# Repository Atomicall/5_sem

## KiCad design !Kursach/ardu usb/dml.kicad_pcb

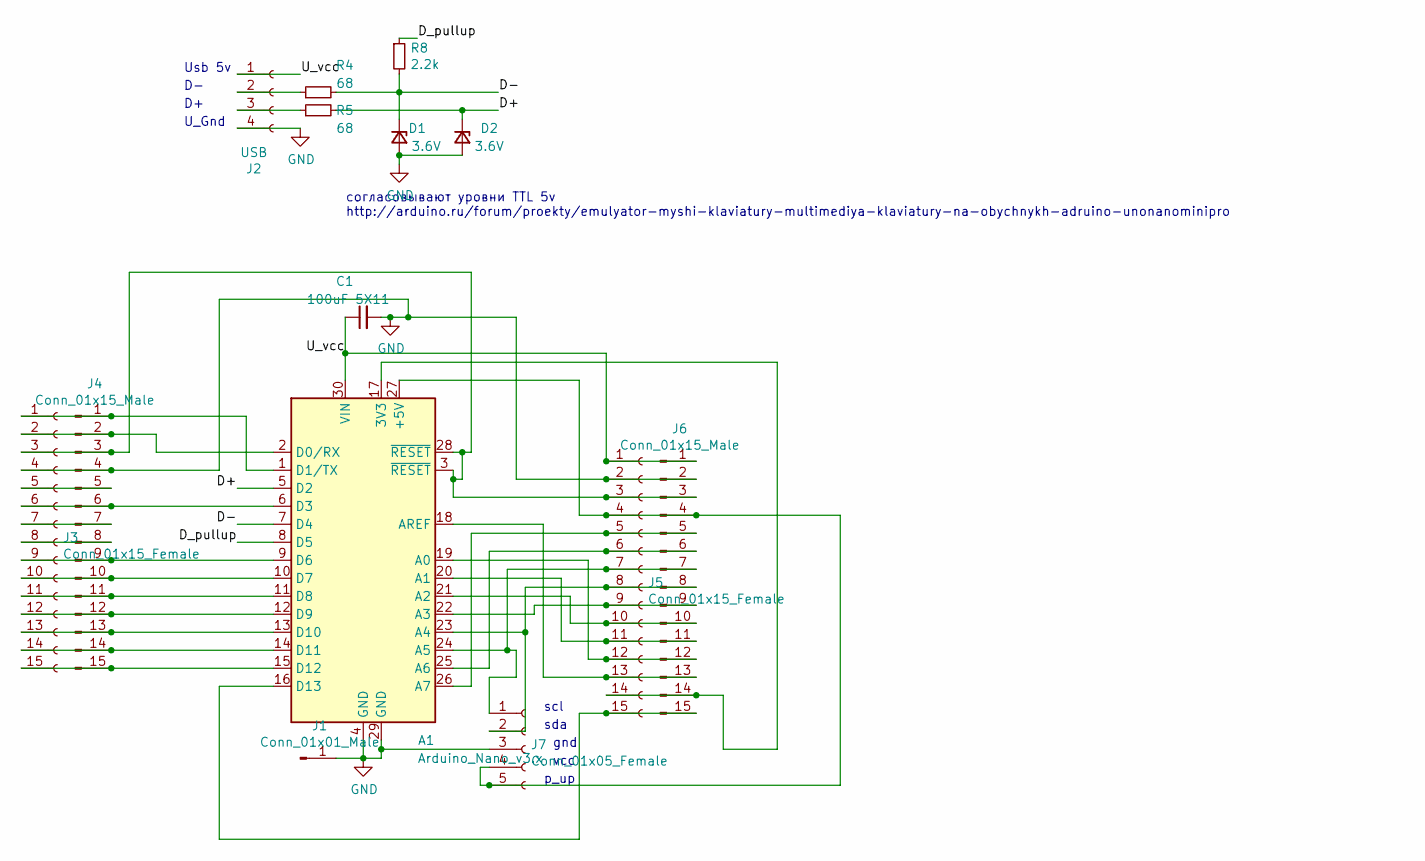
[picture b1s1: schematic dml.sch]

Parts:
A1: Arduino_Nano_v3.x; Arduino_Nano
C1: 100uF 5X11; C_Radial_D5.0mm_H11.0mm_P2.00mm
D1, D2: 3.6V; D_DO-35_SOD27_P7.62mm_Horizontal
J1: Conn_01x01_Male; PinSocket_1x01_P2.54mm_Vertical
J2: USB; usb_type_c_female_board_Aliexpress
J3, J5: Conn_01x15_Female; PinSocket_1x15_P2.54mm_Vertical
J4, J6: Conn_01x15_Male; PinSocket_1x15_P2.54mm_Vertical
J7: Conn_01x05_Female; PinSocket_1x05_P2.54mm_Vertical
R4, R5: 68; R_Axial_DIN0204_L3.6mm_D1.6mm_P2.54mm_Vertical
R8: 2.2k; R_Axial_DIN0204_L3.6mm_D1.6mm_P2.54mm_Vertical

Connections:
/D+: A1.5 (D2), D2.1 (K), R5.2
/D-: A1.7 (D4), D1.1 (K), R4.2, R8.2
/D_pullup: A1.8 (D5), R8.1
/U_vcc: A1.30 (VIN), C1.1, J2.1, J5.1, J6.1
GND: A1.4 (GND), A1.29 (GND), C1.2, D1.2 (A), D2.2 (A), J1.1, J2.4, J3.4, J4.4, J5.2, J6.2, J7.3
unnamed: A1.1 (D1/TX), J3.1, J4.1
unnamed: A1.2 (D0/RX), J3.2, J4.2
unnamed: A1.6 (D3), J3.6, J4.6
unnamed: A1.9 (D6), J3.9, J4.9
unnamed: A1.10 (D7), J3.10, J4.10
unnamed: A1.11 (D8), J3.11, J4.11
unnamed: A1.12 (D9), J3.12, J4.12
unnamed: A1.13 (D10), J3.13, J4.13
unnamed: A1.14 (D11), J3.14, J4.14
unnamed: A1.15 (D12), J3.15, J4.15
unnamed: A1.16 (D13), J5.15, J6.15
unnamed: A1.17 (3V3), J5.14, J6.14
unnamed: A1.18 (AREF), J5.13, J6.13
unnamed: A1.19 (A0), J5.12, J6.12
unnamed: A1.20 (A1), J5.11, J6.11
unnamed: A1.21 (A2), J5.10, J6.10
unnamed: A1.22 (A3), J5.9, J6.9
unnamed: A1.23 (A4), J5.8, J6.8, J7.2
unnamed: A1.24 (A5), J5.7, J6.7, J7.1
unnamed: A1.25 (A6), J5.6, J6.6
unnamed: A1.26 (A7), J5.5, J6.5
unnamed: A1.27 (+5V), J5.4, J6.4, J7.4, J7.5
unnamed: A1.3 (~RESET), A1.28 (~RESET), J3.3, J4.3, J5.3, J6.3
unnamed: J2.2, R4.1
unnamed: J2.3, R5.1
unnamed: J3.5, J4.5
unnamed: J3.7, J4.7
unnamed: J3.8, J4.8

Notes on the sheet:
Usb 5v
U_Gnd
согласовывают уровни TTL 5v http://arduino.ru/forum/proekty/emulyator-myshi-klaviatury-multimediya-klaviatury-na-obychnykh-adruino-unonanominipro
scl
sda
gnd
vcc
p_up

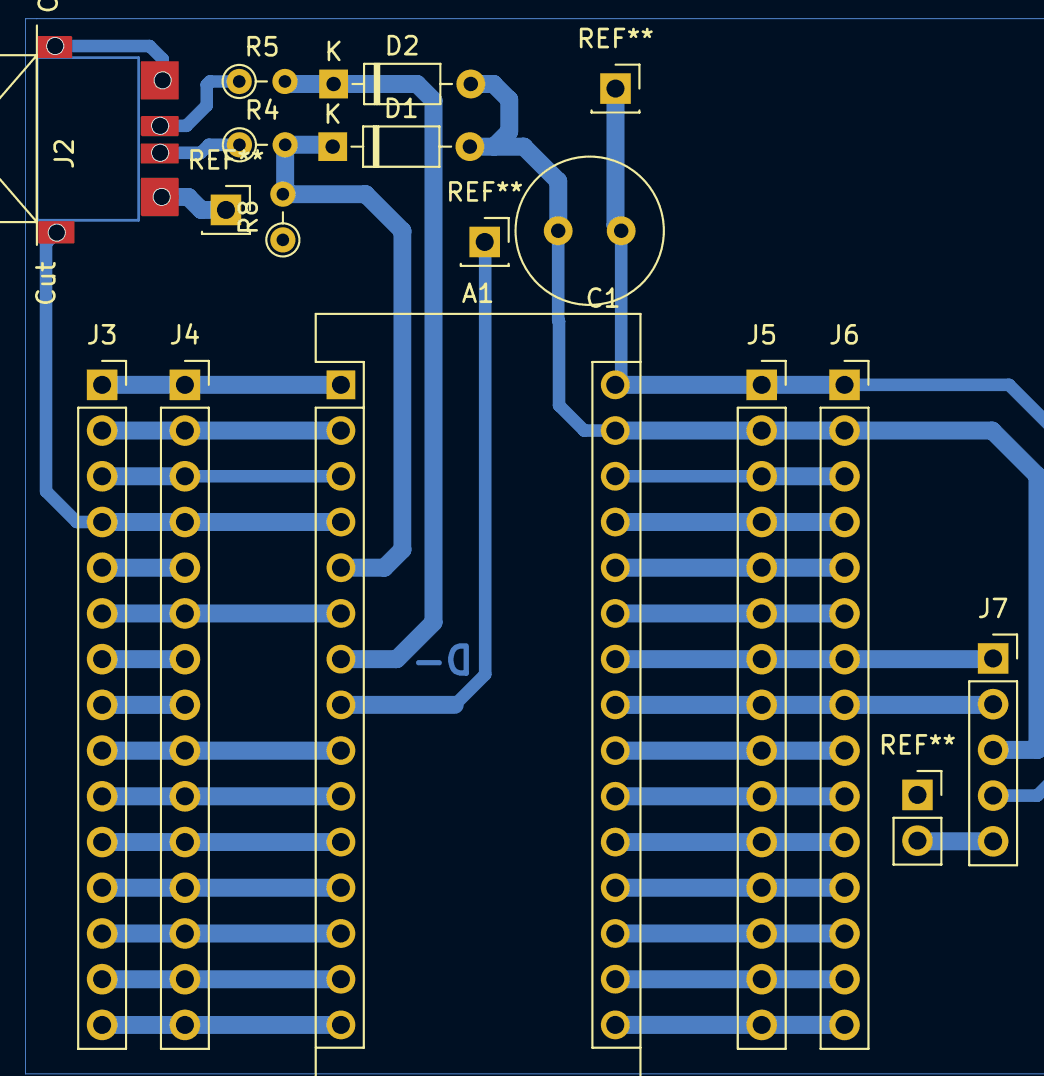
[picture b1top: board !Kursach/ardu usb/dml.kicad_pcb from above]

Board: 2 copper layers, 13 parts (0 on the bottom side), 33 nets.

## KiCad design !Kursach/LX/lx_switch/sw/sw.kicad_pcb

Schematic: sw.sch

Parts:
D1: ss14; D_SMB_Handsoldering
J1: bat; PinSocket_1x02_P2.54mm_Horizontal
J2: usb; PinSocket_1x02_P2.54mm_Horizontal
J3: out; PinSocket_1x02_P2.54mm_Horizontal
Q1: AO3401A; SOT-23
R1: 2.2k; R_1206_3216Metric_Pad1.30x1.75mm_HandSolder

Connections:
GND: J1.2, J2.2, J3.1, R1.2
unnamed: D1.1 (K), J3.2, Q1.2 (S)
unnamed: D1.2 (A), J2.1, Q1.1 (G), R1.1
unnamed: J1.1, Q1.3 (D)

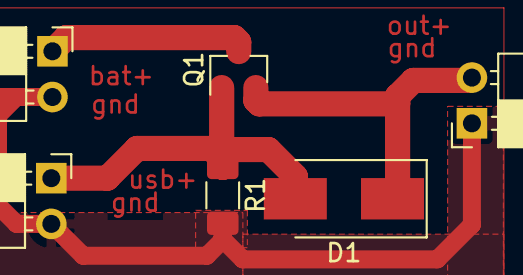
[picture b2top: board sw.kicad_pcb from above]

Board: 2 copper layers, 6 parts (0 on the bottom side), 4 nets.

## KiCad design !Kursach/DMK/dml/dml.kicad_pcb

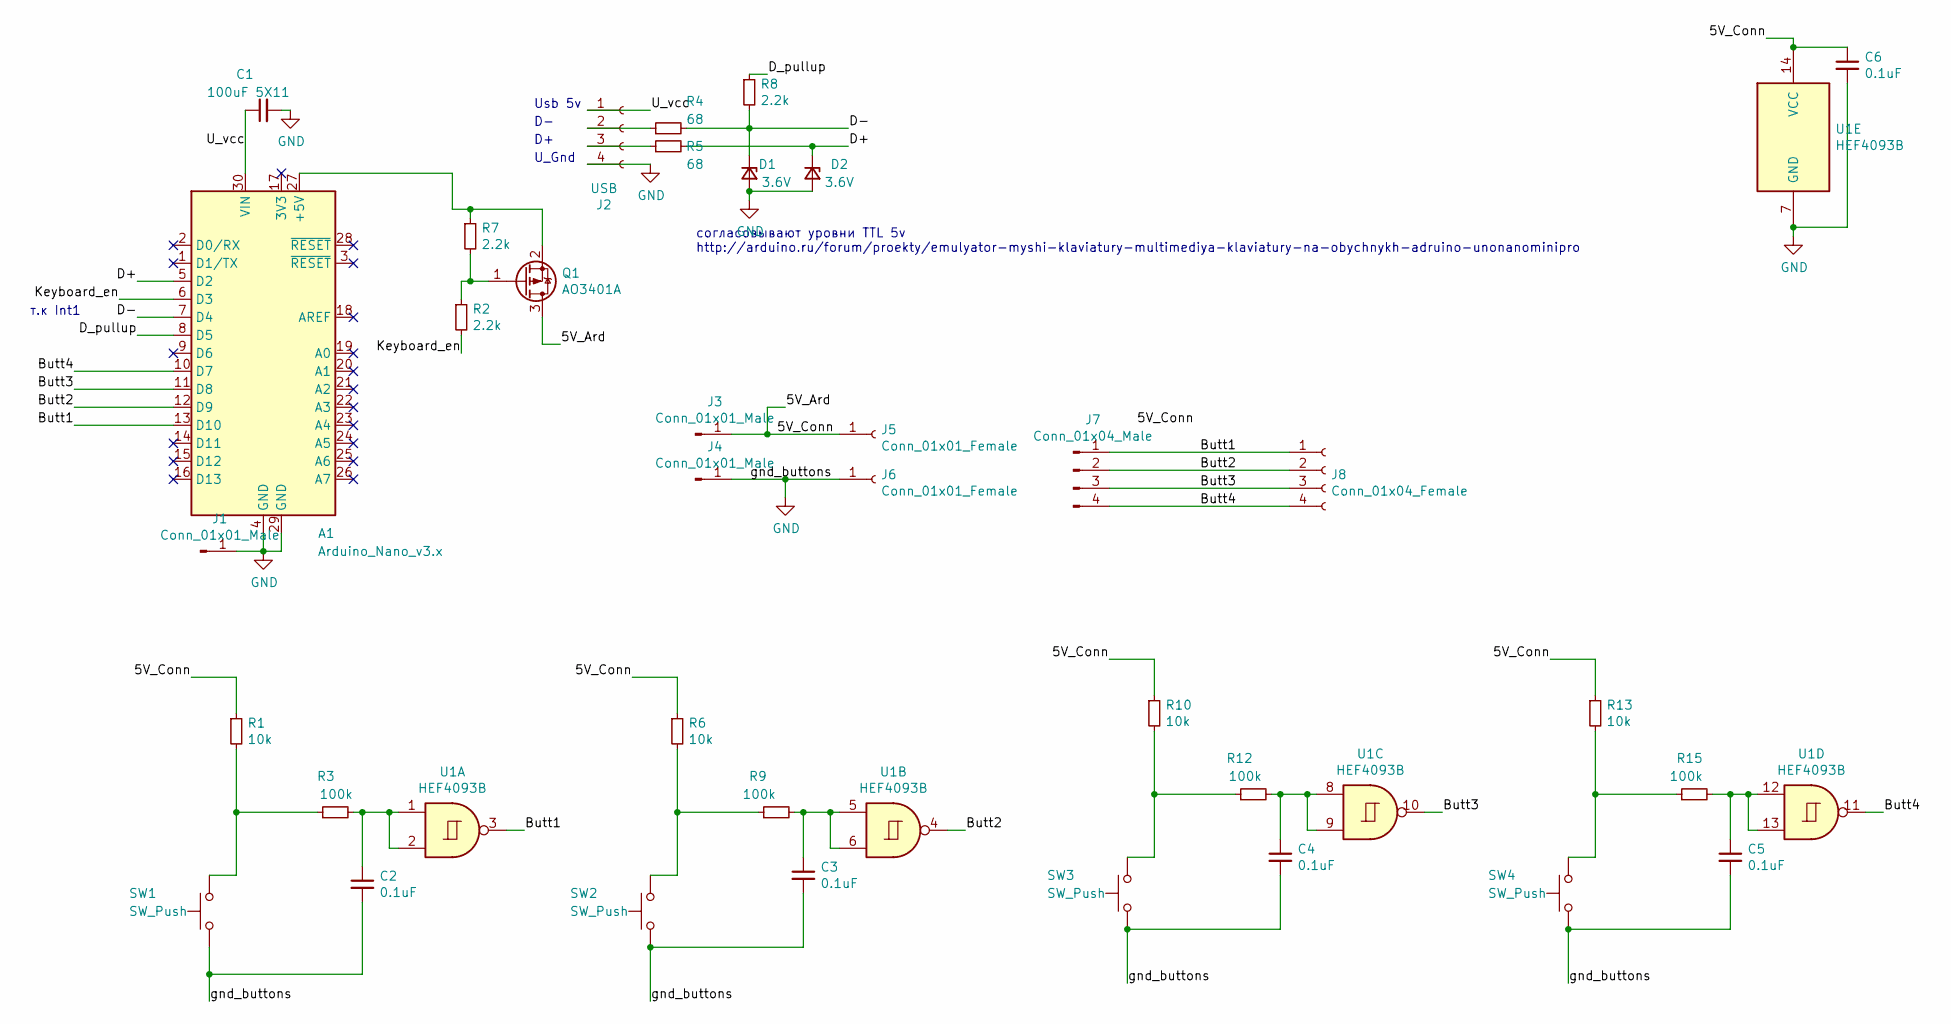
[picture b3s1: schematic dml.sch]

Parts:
A1: Arduino_Nano_v3.x; Arduino_Nano
C1: 100uF 5X11; C_Radial_D5.0mm_H11.0mm_P2.00mm
C2, C3, C4, C5, C6: 0.1uF; C_0805_2012Metric_Pad1.18x1.45mm_HandSolder
D1, D2: 3.6V; D_DO-35_SOD27_P7.62mm_Horizontal
J1: Conn_01x01_Male; PinSocket_1x01_P2.54mm_Vertical
J2: USB; usb_type_c_female_board_Aliexpress
J3, J4: Conn_01x01_Male; PinHeader_1x01_P2.54mm_Vertical
J5, J6: Conn_01x01_Female; PinHeader_1x01_P2.54mm_Vertical
J7: Conn_01x04_Male; PinHeader_1x04_P2.54mm_Vertical
J8: Conn_01x04_Female; PinHeader_1x04_P2.54mm_Vertical
Q1: AO3401A; SOT-23
R1, R6, R10, R13: 10k; R_0805_2012Metric_Pad1.20x1.40mm_HandSolder
R2, R7: 2.2k; R_0805_2012Metric_Pad1.20x1.40mm_HandSolder
R3, R9, R12, R15: 100k; R_0805_2012Metric_Pad1.20x1.40mm_HandSolder
R4, R5: 68; R_Axial_DIN0204_L3.6mm_D1.6mm_P2.54mm_Vertical
R8: 2.2k; R_Axial_DIN0204_L3.6mm_D1.6mm_P2.54mm_Vertical
SW1, SW2, SW3, SW4: SW_Push; SW_Cherry_MX_1.00u_Plate
U1: HEF4093B; SO-14_3.9x8.65mm_P1.27mm

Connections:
/5V_Ard: C6.1, J3.1, J5.1, Q1.3 (D), R1.1, R6.1, R10.1, R13.1, U1.14 (VCC)
/Butt1: A1.13 (D10), J7.1, J8.1, U1.3
/Butt2: A1.12 (D9), J7.2, J8.2, U1.4
/Butt3: A1.11 (D8), J7.3, J8.3, U1.10
/Butt4: A1.10 (D7), J7.4, J8.4, U1.11
/D+: A1.5 (D2), D2.1 (K), R5.2
/D-: A1.7 (D4), D1.1 (K), R4.2, R8.2
/D_pullup: A1.8 (D5), R8.1
/Keyboard_en: A1.6 (D3), R2.2
/U_vcc: A1.30 (VIN), C1.1, J2.1
GND: A1.4 (GND), A1.29 (GND), C1.2, C2.2, C3.2, C4.2, C5.2, C6.2, D1.2 (A), D2.2 (A), J1.1, J2.4, J4.1, J6.1, SW1.1, SW2.1, SW3.1, SW4.1, U1.7 (GND)
unnamed: A1.27 (+5V), Q1.2 (S), R7.1
unnamed: C2.1, R3.2, U1.1, U1.2
unnamed: C3.1, R9.2, U1.5, U1.6
unnamed: C4.1, R12.2, U1.8, U1.9
unnamed: C5.1, R15.2, U1.12, U1.13
unnamed: J2.2, R4.1
unnamed: J2.3, R5.1
unnamed: Q1.1 (G), R2.1, R7.2
unnamed: R1.2, R3.1, SW1.2
unnamed: R6.2, R9.1, SW2.2
unnamed: R10.2, R12.1, SW3.2
unnamed: R13.2, R15.1, SW4.2

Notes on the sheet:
Usb 5v
U_Gnd
согласовывают уровни TTL 5v http://arduino.ru/forum/proekty/emulyator-myshi-klaviatury-multimediya-klaviatury-na-obychnykh-adruino-unonanominipro
т.к Int1

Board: 2 copper layers, 35 parts (0 on the bottom side), 23 nets, no tracks yet.

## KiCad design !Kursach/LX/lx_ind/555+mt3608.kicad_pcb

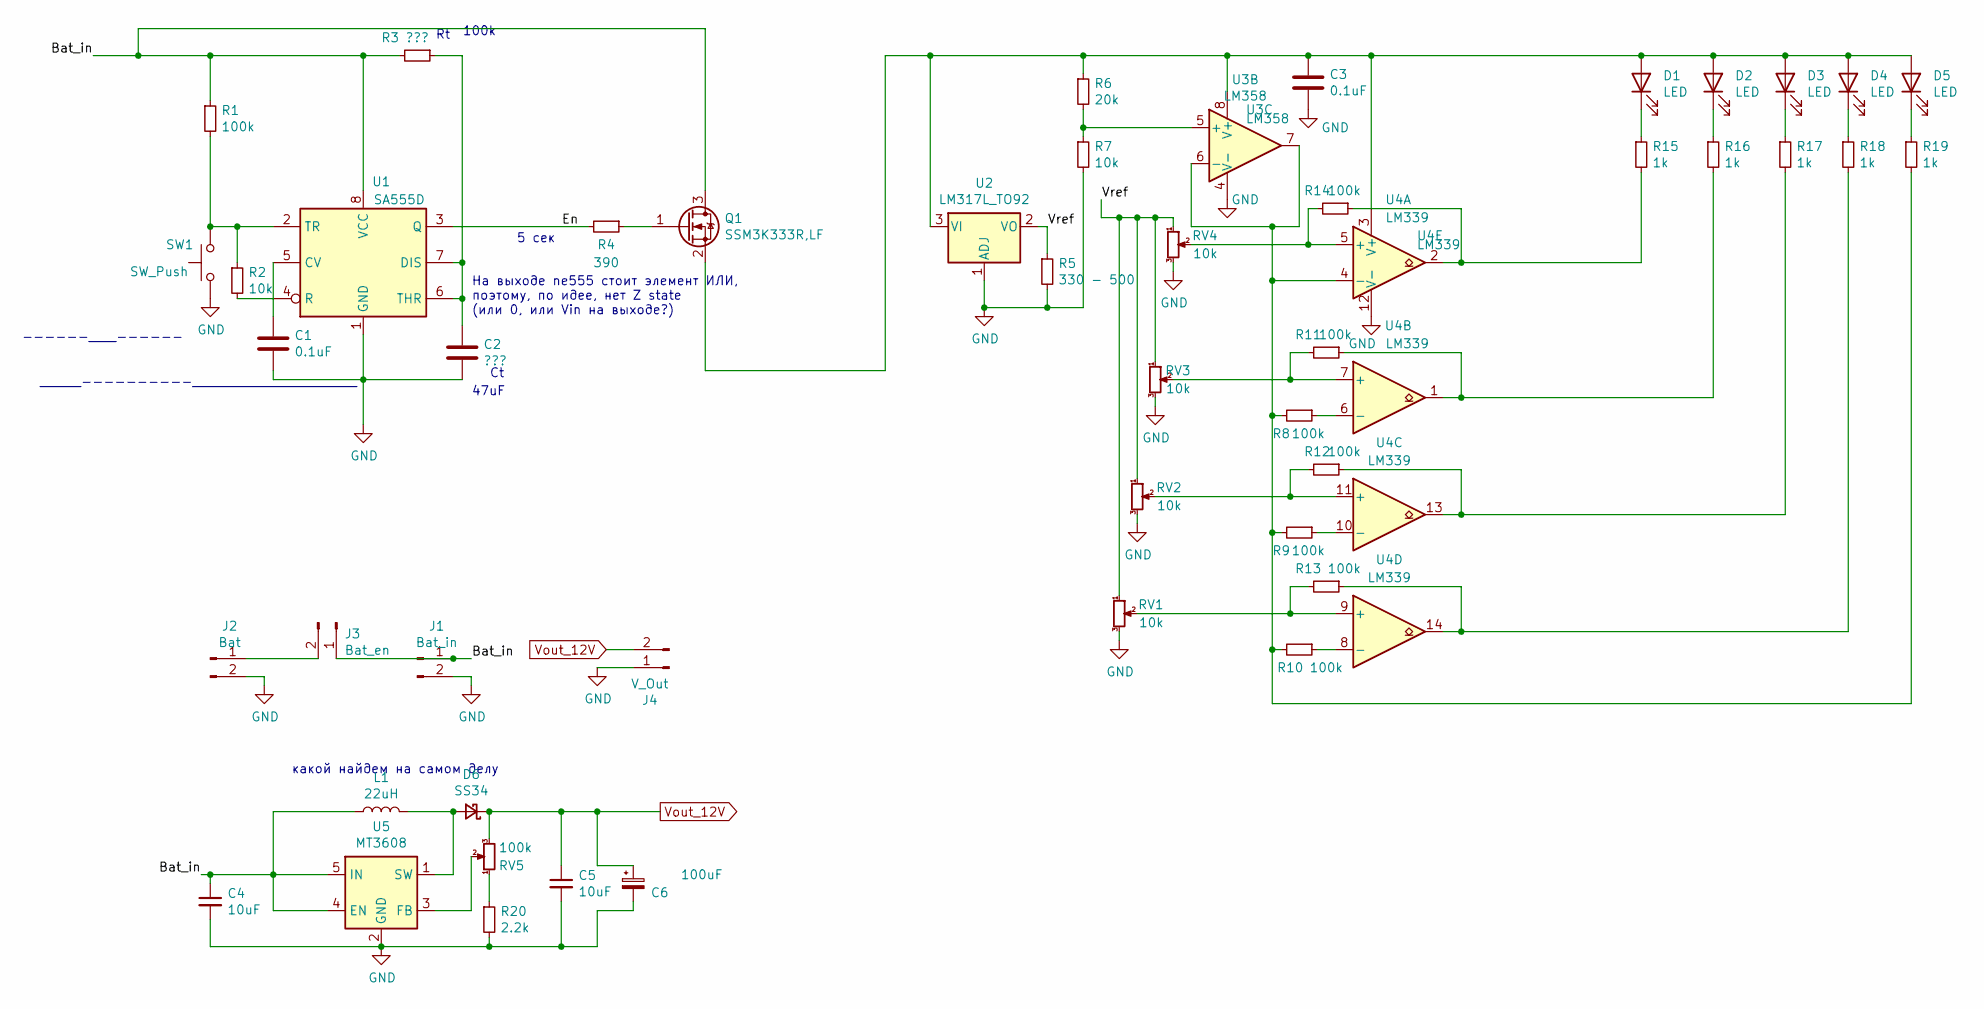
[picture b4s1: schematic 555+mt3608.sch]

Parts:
C1, C3: 0.1uF; C_1206_3216Metric_Pad1.33x1.80mm_HandSolder
C2: ???; CP_EIA-3216-10_Kemet-I_Pad1.58x1.35mm_HandSolder
C4, C5: 10uF; C_1206_3216Metric_Pad1.33x1.80mm_HandSolder
C6: 100uF; CP_Radial_D10.0mm_P5.00mm
D1, D2, D3, D4, D5: LED; LED_1206_3216Metric_Pad1.42x1.75mm_HandSolder
D6: SS34; D_SMC
J1: Bat_in; PinSocket_1x02_P2.54mm_Horizontal
J2: Bat; PinSocket_1x02_P2.54mm_Horizontal
J3: Bat_en; PinSocket_1x02_P2.54mm_Horizontal
J4: V_Out; PinSocket_1x02_P2.54mm_Horizontal
L1: 22uH; L_Bourns_SRR1210A
Q1: SSM3K333R,LF; SOT-23
R1, R8, R9, R10, R11, R12, R13, R14: 100k; R_1206_3216Metric_Pad1.30x1.75mm_HandSolder
R2, R7: 10k; R_1206_3216Metric_Pad1.30x1.75mm_HandSolder
R3: ???; R_1206_3216Metric_Pad1.30x1.75mm_HandSolder
R4: 390; R_1206_3216Metric_Pad1.30x1.75mm_HandSolder
R5: 330 - 500; R_1206_3216Metric_Pad1.30x1.75mm_HandSolder
R6: 20k; R_1206_3216Metric_Pad1.30x1.75mm_HandSolder
R15, R16, R17, R18, R19: 1k; R_1206_3216Metric_Pad1.30x1.75mm_HandSolder
R20: 2.2k; R_1206_3216Metric_Pad1.30x1.75mm_HandSolder
RV1, RV2, RV3, RV4: 10k; Potentiometer_Bourns_TC33X_Vertical
RV5: 100k; Potentiometer_Bourns_TC33X_Vertical
SW1: SW_Push; SW_SPST_EVPBF
U1: SA555D; SOIC-8_3.9x4.9mm_P1.27mm
U2: LM317L_TO92; TO-92_Inline
U3: LM358; SO-8_3.9x4.9mm_P1.27mm
U4: LM339; SO-14_3.9x8.65mm_P1.27mm
U5: MT3608; SOT-23-6_Handsoldering

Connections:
/Bat_in: C4.1, J1.1, J3.1, L1.1, Q1.3 (D), R1.1, R3.2, U1.8 (VCC), U5.4 (EN), U5.5 (IN)
/En: R4.2, U1.3 (Q)
/Vref: R5.1, RV1.1, RV2.1, RV3.1, RV4.1, U2.2 (VO)
GND: C1.2, C2.2, C3.2, C4.2, C5.2, C6.2, J1.2, J2.2, J4.1, R5.2, R7.2, R20.2, RV1.3, RV2.3, RV3.3, RV4.3, SW1.1, U1.1 (GND), U2.1 (ADJ), U3.4 (V-), U4.12 (V-), U5.2 (GND)
unnamed: C1.1, U1.5 (CV)
unnamed: C2.1, R3.1, U1.6 (THR), U1.7 (DIS)
unnamed: C3.1, D1.2 (A), D2.2 (A), D3.2 (A), D4.2 (A), D5.2 (A), Q1.2 (S), R6.1, U2.3 (VI), U3.8 (V+), U4.3 (V+)
unnamed: D1.1 (K), R15.1
unnamed: D2.1 (K), R16.1
unnamed: D3.1 (K), R17.1
unnamed: D4.1 (K), R18.1
unnamed: D5.1 (K), R19.1
unnamed: D6.2 (A), L1.2, U5.1 (SW)
unnamed: J2.1, J3.2
unnamed: Q1.1 (G), R4.1
unnamed: R1.2, R2.1, SW1.2, U1.2 (TR)
unnamed: R2.2, U1.4 (R)
unnamed: R6.2, R7.1, U3.5 (+)
unnamed: R8.1, U4.6 (-)
unnamed: R9.1, U4.10 (-)
unnamed: R10.1, U4.8 (-)
unnamed: R8.2, R9.2, R10.2, R19.2, U3.6 (-), U3.7, U4.4 (-)
unnamed: R11.1, R16.2, U4.1
unnamed: R11.2, RV3.2, U4.7 (+)
unnamed: R12.1, R17.2, U4.13
unnamed: R12.2, RV2.2, U4.11 (+)
unnamed: R13.1, R18.2, U4.14
unnamed: R13.2, RV1.2, U4.9 (+)
unnamed: R14.1, R15.2, U4.2
unnamed: R14.2, RV4.2, U4.5 (+)
unnamed: R20.1, RV5.1
unnamed: RV5.2, U5.3 (FB)
Vout_12V: C5.1, C6.1, D6.1 (K), J4.2, RV5.3

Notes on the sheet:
------____------
______----------________________________
100k
47uF
5 сек
На выходе ne555 стоит элемент ИЛИ, поэтому, по идее, нет Z state (или 0, или Vin на выходе?)
какой найдем на самом делу

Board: 2 copper layers, 49 parts (0 on the bottom side), 33 nets, no tracks yet.

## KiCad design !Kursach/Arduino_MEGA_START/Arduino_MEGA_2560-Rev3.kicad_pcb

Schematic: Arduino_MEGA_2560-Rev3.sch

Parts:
ADCH1: 8x1F-H8.5; SMARTPRJ_1X08
ADCL1: 8x1F-H8.5; SMARTPRJ_1X08
COMMUNICATION1: 8x1F-H8.5; SMARTPRJ_1X08
J1: RX; PinHeader_1x02_P2.54mm_Vertical
J2: TX; PinHeader_1x02_P2.54mm_Vertical
J3: Midi_UART; PinHeader_1x03_P2.54mm_Vertical
J4: USB_Uart; PinHeader_1x03_P2.54mm_Vertical
J5: Power_conn; PinHeader_1x02_P2.54mm_Vertical
POWER1: 8x1F-H8.5; SMARTPRJ_1X08
PWMH1: 8x1F-H8.5; PinHeader_1x08_P2.54mm_Vertical
PWML1: 8x1F-H8.5; SMARTPRJ_1X08
XIO1: 18x2F-H8.5; SMARTPRJ_2X18

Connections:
/+3V3: POWER1.4
/+5V: POWER1.2, POWER1.5
/ADC0: ADCL1.1
/ADC1: ADCL1.2
/ADC2: ADCL1.3
/ADC3: ADCL1.4
/ADC4: ADCL1.5
/ADC5: ADCL1.6
/ADC6: ADCL1.7
/ADC7: ADCL1.8
/ADC8: ADCH1.1
/ADC9: ADCH1.2
/ADC10: ADCH1.3
/ADC11: ADCH1.4
/ADC12: ADCH1.5
/ADC13: ADCH1.6
/ADC14: ADCH1.7
/ADC15: ADCH1.8
/Aref: PWMH1.8
/Dir1: XIO1.3; also elsewhere on the board
/Dir2: XIO1.7; also elsewhere on the board
/Dir3: XIO1.11; also elsewhere on the board
/Dir4: XIO1.15; also elsewhere on the board
/Dir5: XIO1.19; also elsewhere on the board
/Dir6: XIO1.23; also elsewhere on the board
/Dir7: XIO1.27; also elsewhere on the board
/Dir8: XIO1.31; also elsewhere on the board
/Dir9: XIO1.4; also elsewhere on the board
/Dir10: XIO1.8; also elsewhere on the board
/Dir11: XIO1.12; also elsewhere on the board
/Dir12: XIO1.16; also elsewhere on the board
/Dir13: XIO1.20; also elsewhere on the board
/Dir14: XIO1.24; also elsewhere on the board
/Dir15: XIO1.28; also elsewhere on the board
/Dir16: XIO1.32; also elsewhere on the board
/Dir17: PWML1.3; also elsewhere on the board
/Dir18: PWML1.5; also elsewhere on the board
/P24: XIO1.5; also elsewhere on the board
/P25: XIO1.6; also elsewhere on the board
/P28: XIO1.9; also elsewhere on the board
/P29: XIO1.10; also elsewhere on the board
/P32: XIO1.13; also elsewhere on the board
/P33: XIO1.14; also elsewhere on the board
/P36: XIO1.17; also elsewhere on the board
/P37: XIO1.18; also elsewhere on the board
/P40: XIO1.21; also elsewhere on the board
/P41: XIO1.22; also elsewhere on the board
/P44: XIO1.25; also elsewhere on the board
/P45: XIO1.26; also elsewhere on the board
/P48: XIO1.29; also elsewhere on the board
/P49: XIO1.30; also elsewhere on the board
/P52: XIO1.33; also elsewhere on the board
/P53: XIO1.34; also elsewhere on the board
/PB4: PWMH1.3
/PB5: PWMH1.4
/PB6: PWMH1.5
/PB7: PWMH1.6
/PE0: J1.2, PWML1.1
/PE1: J2.2, PWML1.2
/PE3: PWML1.6; also elsewhere on the board
/PE5: PWML1.4; also elsewhere on the board
/PH3: PWML1.7
/PH4: PWML1.8
/PH5: PWMH1.1
/PH6: PWMH1.2
/RESET: POWER1.3
/RXD1: COMMUNICATION1.3
/RXD2: COMMUNICATION1.5, J4.2
/RXD3: COMMUNICATION1.7, J3.2
/SCL: COMMUNICATION1.1
/SDA: COMMUNICATION1.2
/TXD1: COMMUNICATION1.4
/TXD2: COMMUNICATION1.6, J4.3
/TXD3: COMMUNICATION1.8, J3.3
/VIN: J5.2, POWER1.8
GND: J3.1, J4.1, J5.1, POWER1.6, POWER1.7, PWMH1.7, XIO1.35, XIO1.36

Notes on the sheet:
AREF

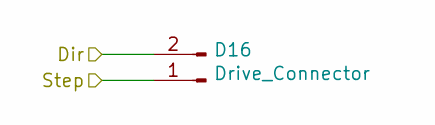
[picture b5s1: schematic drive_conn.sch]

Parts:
D1: Drive_Connector; PinHeader_1x02_P2.54mm_Vertical

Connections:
/Dir1: D1.2; also elsewhere on the board
/P24: D1.1; also elsewhere on the board

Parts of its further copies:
D2, D3, D4, D5, D6, D7, D8, D9, D10, D11, D12, D13, D14, D15, D16, D17, D18: Drive_Connector; PinHeader_1x02_P2.54mm_Vertical

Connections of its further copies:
/Dir2: D2.2; also elsewhere on the board
/Dir3: D3.2; also elsewhere on the board
/Dir4: D4.2; also elsewhere on the board
/Dir5: D5.2; also elsewhere on the board
/Dir6: D6.2; also elsewhere on the board
/Dir7: D7.2; also elsewhere on the board
/Dir8: D8.2; also elsewhere on the board
/Dir9: D9.2; also elsewhere on the board
/Dir10: D10.2; also elsewhere on the board
/Dir11: D11.2; also elsewhere on the board
/Dir12: D12.2; also elsewhere on the board
/Dir13: D13.2; also elsewhere on the board
/Dir14: D14.2; also elsewhere on the board
/Dir15: D15.2; also elsewhere on the board
/Dir16: D18.2; also elsewhere on the board
/Dir17: D16.2; also elsewhere on the board
/Dir18: D17.2; also elsewhere on the board
/P25: D9.1; also elsewhere on the board
/P28: D2.1; also elsewhere on the board
/P29: D10.1; also elsewhere on the board
/P32: D3.1; also elsewhere on the board
/P33: D11.1; also elsewhere on the board
/P36: D4.1; also elsewhere on the board
/P37: D12.1; also elsewhere on the board
/P40: D5.1; also elsewhere on the board
/P41: D13.1; also elsewhere on the board
/P44: D6.1; also elsewhere on the board
/P45: D14.1; also elsewhere on the board
/P48: D7.1; also elsewhere on the board
/P49: D15.1; also elsewhere on the board
/P52: D8.1; also elsewhere on the board
/P53: D18.1; also elsewhere on the board
/PE3: D17.1; also elsewhere on the board
/PE5: D16.1; also elsewhere on the board

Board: 2 copper layers, 30 parts (0 on the bottom side), 45 nets, no tracks yet.

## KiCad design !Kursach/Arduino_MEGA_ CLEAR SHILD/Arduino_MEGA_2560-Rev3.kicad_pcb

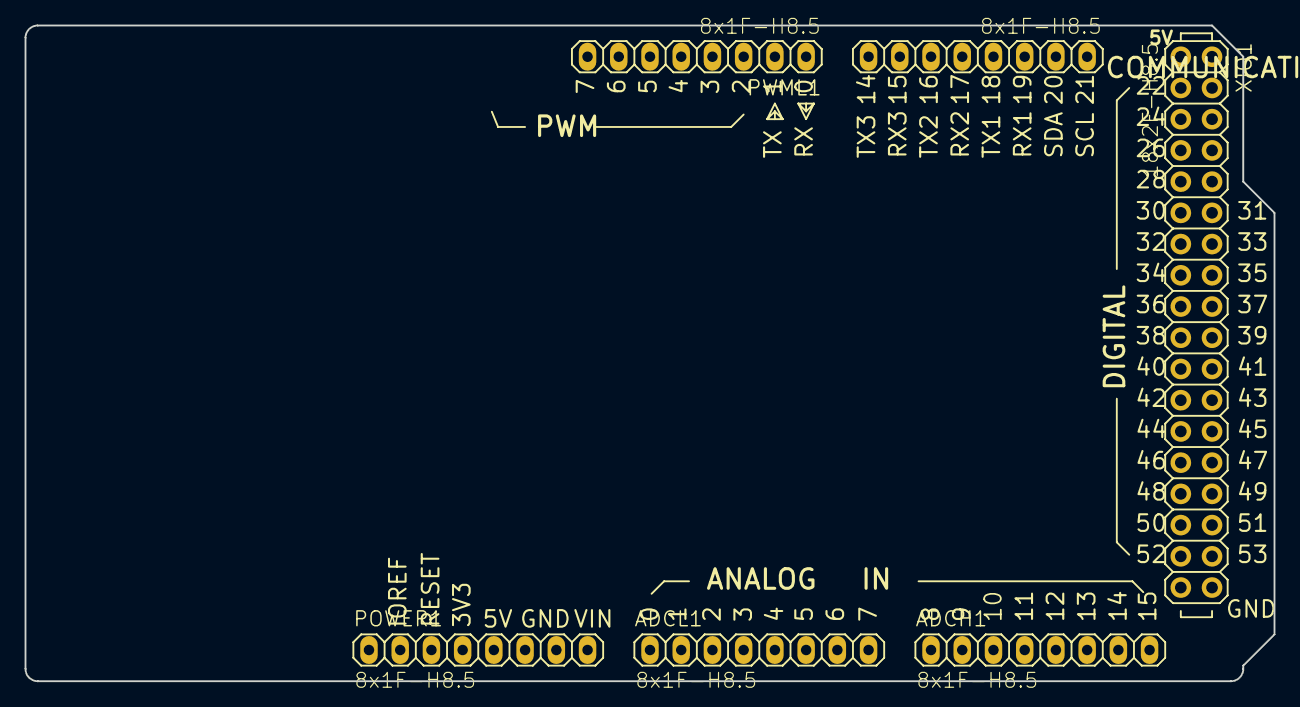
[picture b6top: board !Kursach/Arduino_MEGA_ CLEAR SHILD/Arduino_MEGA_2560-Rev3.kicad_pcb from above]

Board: 2 copper layers, 101.6 x 53.3 mm, 6 parts (0 on the bottom side), 2 nets, no tracks yet.

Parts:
ADCH1: 8x1F-H8.5; 1X08
ADCL1: 8x1F-H8.5; 1X08
COMMUNICATION1: 8x1F-H8.5; 1X08
POWER1: 8x1F-H8.5; 1X08
PWML1: 8x1F-H8.5; 1X08
XIO1: 18x2F-H8.5; 2X18

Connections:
/+5V: POWER1.2, POWER1.5, XIO1.1, XIO1.2
/GND: POWER1.6, POWER1.7, XIO1.35, XIO1.36

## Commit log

2021-10-06 lab 2 toks
2021-10-06 Lab 2 toks with bugs
2021-10-09 Lab2 Sifo done
2021-10-11 floppatron
2021-10-25 var res 100k error
2021-10-30 lx v2
2021-11-03 iipu 4 added + refs
2021-12-05 fuck
2021-12-06 PAIN
2021-12-07 shit
2021-12-08 help
2021-12-09 ыыыыыы
